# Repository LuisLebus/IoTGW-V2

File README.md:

<div id="top">

</div>

<!-- LOGO AND TITTLE -->
<div align="center">
  <h3 align="center">Luis Lebus</h3>

  [![LinkedIn][linkedin-shield]][linkedin-url]
  [![Portfolio][portfolio-shield]][portfolio-url]
  
  <br>
  
  <h3 align="center">IoTGW-V2</h3>
  <p align="center">Gateway IoT V2</p>
</div>

<!-- TABLE OF CONTENTS -->
<details>
  <summary>Table of Contents</summary>
  <ol>
    <li>
      <a href="#description">Description</a>
      <ul>
        <li><a href="#built-with">Built With</a></li>
      </ul>
    </li>
    <li><a href="#image">Image</a></li>
    <li><a href="#contact">Contact</a></li>
    <li><a href="#acknowledgments">Acknowledgments</a></li>
  </ol>
</details>

<!-- ABOUT THE PROJECT -->
## Description

This project is an IoT gateway. 
<br>
This board has CAN, Modbus RTU, WiFi and Ethernet communication.

<p align="right">(<a href="#top">back to top</a>)</p>

### Built With

* [KiCad v5.1.12](https://www.kicad.org/)

<p align="right">(<a href="#top">back to top</a>)</p>

<!-- ABOUT THE PROJECT -->
## Image

<p align="right">(<a href="#top">back to top</a>)</p>

<!-- CONTACT -->
## Contact

Luis Lebus - luislebus@gmail.com

* [LinkedIn](https://www.linkedin.com/in/LuisLebus)
* [Portfolio](https://luislebus.github.io/portfolio)

<p align="right">(<a href="#top">back to top</a>)</p>

<!-- ACKNOWLEDGMENTS -->
## Acknowledgments

<p align="right">(<a href="#top">back to top</a>)</p>

<!-- MARKDOWN LINKS & IMAGES -->
[linkedin-shield]: https://img.shields.io/badge/LinkedIn-0077B5?style=for-the-badge&logo=linkedin&logoColor=white
[linkedin-url]: https://www.linkedin.com/in/LuisLebus
[portfolio-shield]: https://img.shields.io/badge/PORTFOLIO%20-%23323330.svg?&style=for-the-badge&logo=badges&logoColor=black&color=0000FF
[portfolio-url]: https://luislebus.github.io/portfolio

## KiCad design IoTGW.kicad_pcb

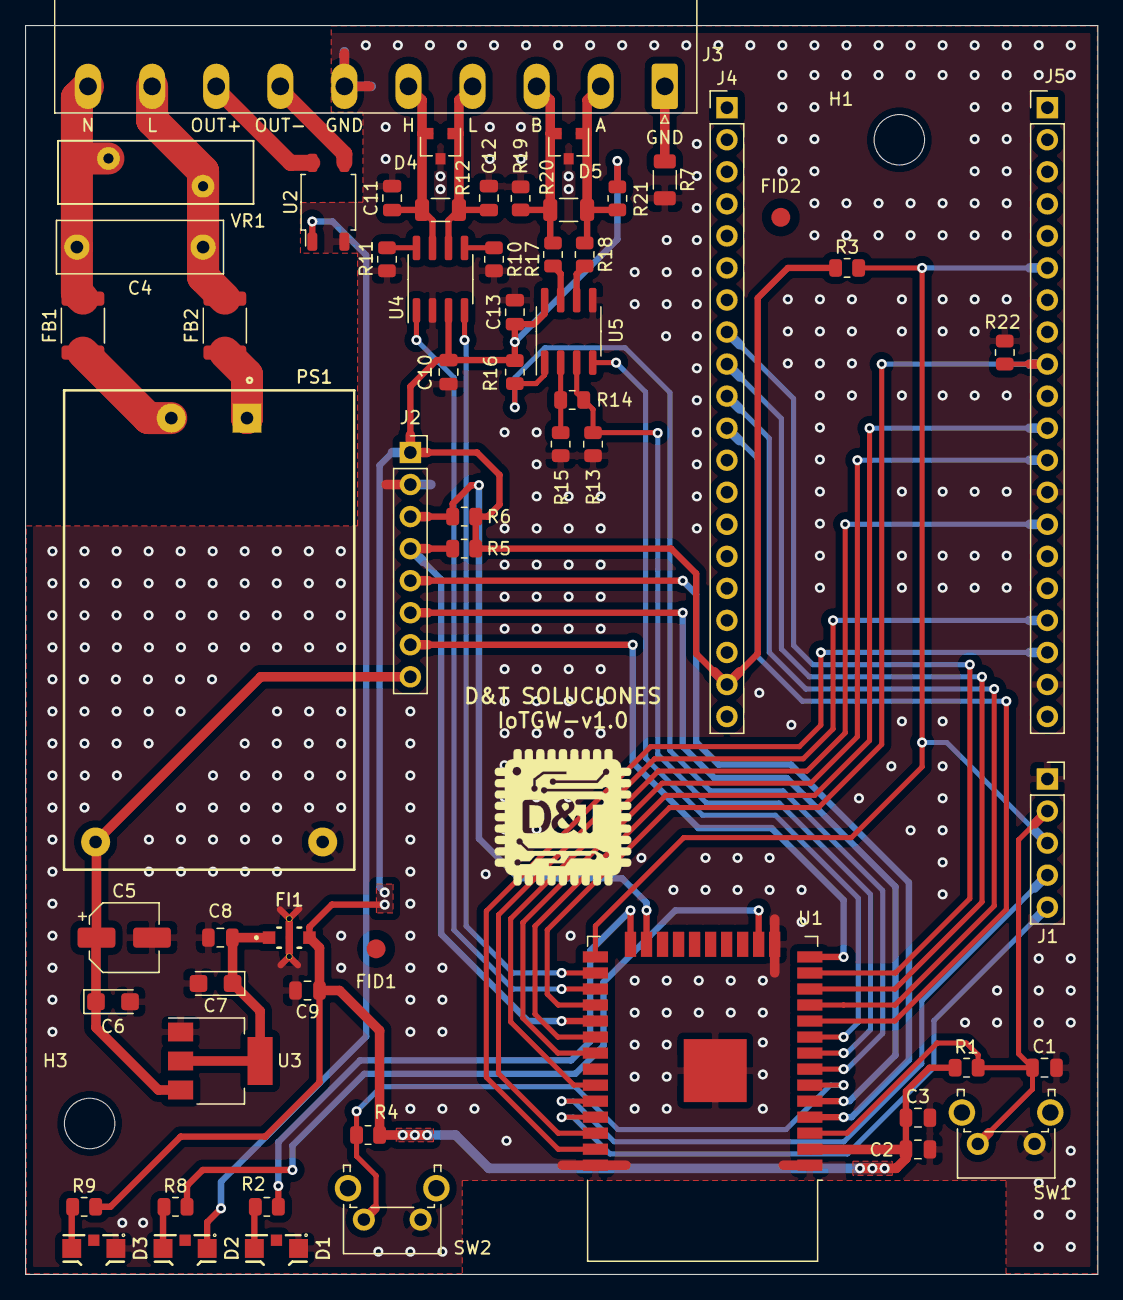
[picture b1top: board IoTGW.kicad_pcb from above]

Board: 2 copper layers, 85.0 x 99.0 mm, 61 parts (0 on the bottom side), 51 nets.

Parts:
C1, C2, C3, C8, C9, C10, C13: 100nF; C_0805_2012Metric
C4: 10nF/330V Poly; C_Rect_L13.0mm_W4.0mm_P10.00mm_FKS3_FKP3_MKS4
C5: 47uF/16V; CP_Elec_5x5.4
C6, C7: 10uF/10V Tant; CP_EIA-3216-18_Kemet-A
C11, C12: 47pF; C_0805_2012Metric
D1, D2, D3: RED; LTST-S321KRKT
D4: PESD2CAN; SOT-23
D5: SM712; SOT-23
FB1, FB2: HI1812V101R-10; L_1812_4532Metric
FI1: NFE31PT222Z1E9L
FID1, FID2: Fiducial; Fiducial_1.5mm_Mask3mm
H1, H3: MountingHole_4mm
J1: PROG; PinSocket_1x05_P2.54mm_Vertical
J2: AUX; PinSocket_1x08_P2.54mm_Vertical
J3: CON; 1759091
J4, J5: ETH; PinHeader_1x20_P2.54mm_Vertical
PS1: HLK-5M05
R1, R5, R6: 10K; R_0805_2012Metric
R2, R9: 470R; R_0805_2012Metric
R3, R4, R10, R11, R13, R15, R16, R22: 4K7; R_0805_2012Metric
R7: 100R; R_1206_3216Metric
R8: 47R; R_0805_2012Metric
R12, R20: 120R; R_1206_3216Metric
R14: 0R; R_0805_2012Metric
R17, R18: 10R; R_0805_2012Metric
R19, R21: 560R; R_0805_2012Metric
SW1, SW2: SW; SW_Tactile_SPST_Angled_PTS645Vx83-2LFS
U1: ESP32-WROOM-32
U2: PS2702-1; PS2702-1-F3-K-A
U3: LM1117-3.3; SOT-223-3_TabPin2
U4: TCAN334D; SOIC-8_3.9x4.9mm_P1.27mm
U5: SN65HVD10; SOIC-8_3.9x4.9mm_P1.27mm
VR1: S14K275; RV_Disc_D15.5mm_W5mm_P7.5mm

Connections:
485_A: D5.1, J3.2, R18.1, R20.2, R21.1
485_B: D5.2, J3.3, R17.1, R19.2, R20.1
485_RTS: R13.1, R14.1, U1.8, U5.3
485_RX: R16.2, U1.7, U5.1
485_TX: U1.9, U5.4
+3.3V: C2.1, C3.1, C9.1, C10.1, C13.1, FI1.3, J2.1, J4.19, R1.1, R3.1, R4.1, R5.1, R6.1, R9.2, R16.1, R21.2, U1.2, U4.3, U5.8
+5V: C5.1, C6.1, J2.8, PS1.4, U3.3
/AUX0: J2.3, R6.2, U1.23
/AUX1: J2.4, R5.2, U1.29
/AUX2: J2.5, U1.4
/AUX3: J2.6, U1.5
/AUX4: J2.7, U1.14
/EN: C1.1, J1.2, R1.2, SW1.2, U1.3
/LED1: R2.1, U1.24
/OUTPUT: R8.2, U1.16
/OUTPUT+: J3.8, U2.4
/OUTPUT-: J3.7, U2.3
/RXD0: J1.4, U1.34
/SW_WEB: R4.2, SW2.2, U1.6
/TXD0: J1.5, U1.35
AC_L: C4.1, FB2.2, J3.9, VR1.1
AC_N: C4.2, FB1.2, J3.10, VR1.2
CAN_H: C11.1, D4.2, J3.5, R12.1, U4.7
CAN_L: C12.1, D4.1, J3.4, R12.2, U4.6
CAN_RX: U1.26, U4.4
CAN_TX: U1.27, U4.1
ETH_CLK: J1.3, J5.6, R3.2, U1.25
ETH_CRS: J4.9, U1.12
ETH_DV: J4.8, U1.13
ETH_MDC: J5.18, U1.37
ETH_MDIO: J5.11, U1.30
ETH_POWER: J5.9, R22.1, U1.28
ETH_RXD0: J4.11, U1.10
ETH_RXD1: J4.10, U1.11
ETH_TXD0: J5.12, U1.31
ETH_TXD1: J5.17, U1.36
ETH_TX_EN: J5.14, U1.33
GND: C1.2, C2.2, C3.2, C5.2, C6.2, C7.2, C8.2, C9.2, C10.2, C11.2, C12.2, C13.2, D1.1, D3.1, D4.3, D5.3, FI1.2, J1.1, J2.2, J3.6, J5.13, J5.19, PS1.3, R7.2, R10.2, R11.2, R13.2, R15.2, R19.1, R22.2, SW1.1, SW2.1, U1.1, U1.15, U1.38, U1.39, U2.2, U3.1, U4.2, U5.5
unnamed: C7.1, C8.1, FI1.1, U3.2
unnamed: D1.2, R2.2
unnamed: D2.1, U2.1
unnamed: D2.2, R8.1
unnamed: D3.2, R9.1
unnamed: FB1.1, PS1.2
unnamed: FB2.1, PS1.1
unnamed: J3.1, R7.1
unnamed: R10.1, U4.5
unnamed: R11.1, U4.8
unnamed: R14.2, R15.1, U5.2
unnamed: R17.2, U5.7
unnamed: R18.2, U5.6
